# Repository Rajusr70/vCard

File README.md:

# vCard
vCard is an business card with 12 x 8 LED-Matrix (total 96 LEDs) and microcontroller.
The device is pre-programmed with the Arduino Bootloader and powered by a CR2032 button cell.

## Shop
* [vCard](http://www.watterott.com/en/V-Card)

## Hardware
* 
* [Schematics + Layout](https://github.com/watterott/vCard/tree/master/pcb)
* **Note: When using an external power supply (eg via the FTDI port) always remove the battery.**

## Software
* [Arduino Examples](https://github.com/watterott/vCard/tree/master/src)
* [vCard Online Frame Editor](http://vcard.pipefishbook.com/)

## Videos

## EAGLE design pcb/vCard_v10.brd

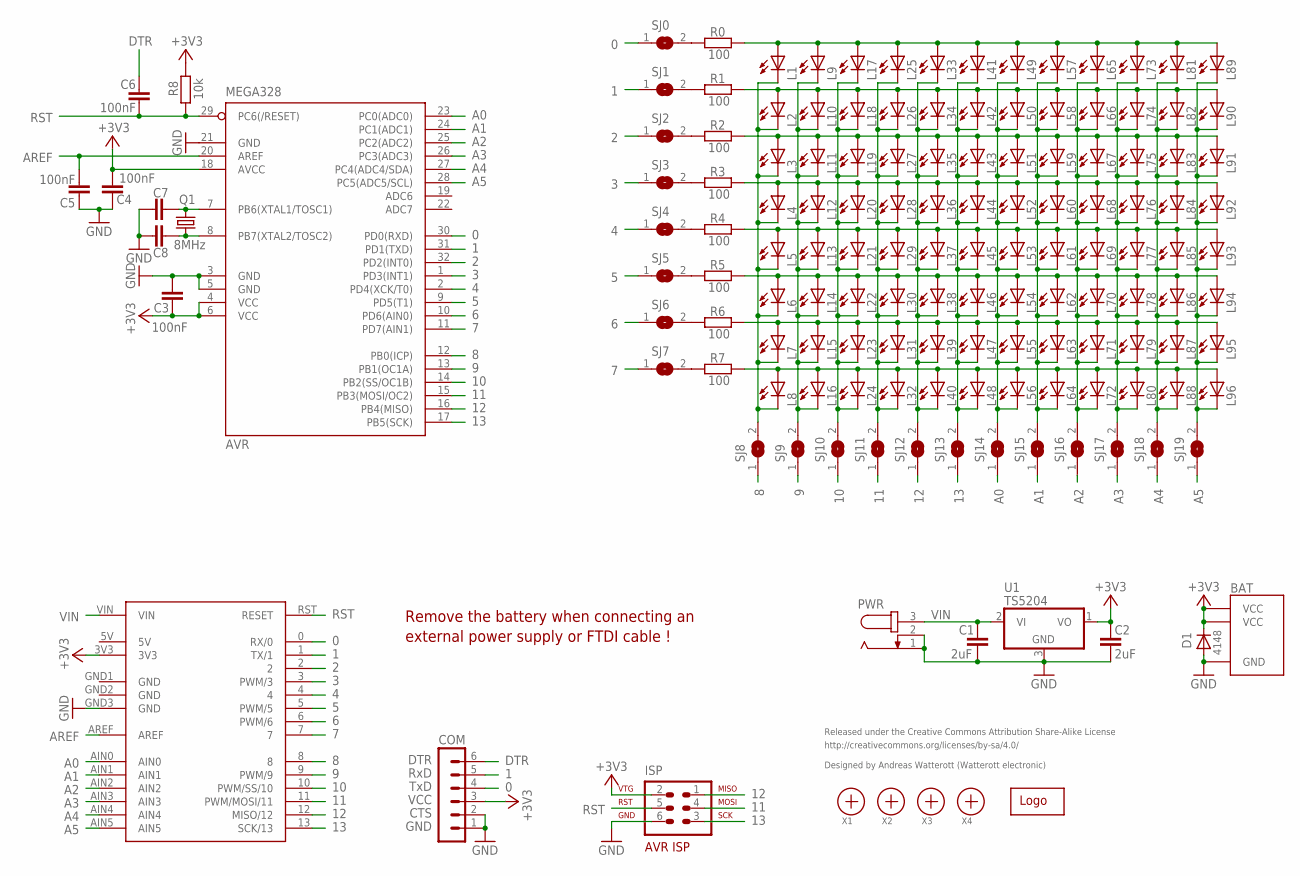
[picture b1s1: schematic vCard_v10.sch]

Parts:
ARDUINO: UNO; DUEMILANOVE2
AVR: MEGA328; TQFP32-08
BAT: KC3002S
C1, C2: 2uF; C0603
C3, C4, C5, C6: 100nF; C0603
C7, C8: C-EUC0603; C0603
COM: MA06-1
D1: 4148; MLL34
ISP: AVR-ISP-6
L1, L2, L3, L4, L5, L6, L7, L8, L9, L10, L11, L12, L13, L14, L15, L16, L17, L18, L19, L20, L21, L22, L23, L24, L25, L26, L27, L28, L29, L30, L31, L32, L33, L34, L35, L36, L37, L38, L39, L40, L41, L42, L43, L44, L45, L46, L47, L48, L49, L50, L51, L52, L53, L54, L55, L56, L57, L58, L59, L60, L61, L62, L63, L64, L65, L66, L67, L68, L69, L70, L71, L72, L73, L74, L75, L76, L77, L78, L79, L80, L81, L82, L83, L84, L85, L86, L87, L88, L89, L90, L91, L92, L93, L94, L95, L96: LEDCHIPLED_0603; CHIPLED_0603
LOGO1: WE-LOGO
PWR: JACK-PLUG0; SPC4077
Q1: 8MHz; HC49/S
R0, R1, R2, R3, R4, R5, R6, R7: 100; R0603
R8: 10k; R0603
SJ0, SJ1, SJ2, SJ3, SJ4, SJ5, SJ6, SJ7, SJ8, SJ9, SJ10, SJ11, SJ12, SJ13, SJ14, SJ15, SJ16, SJ17, SJ18, SJ19: SJ
U1: TS5204; SOT23
X1, X2, X3, X4: PASSER

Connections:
0: ARDUINO.0 (RX/0), AVR.30 (PD0(RXD)), COM.4, SJ0.1
1: ARDUINO.1 (TX/1), AVR.31 (PD1(TXD)), COM.5, SJ1.1
2: ARDUINO.2, AVR.32 (PD2(INT0)), SJ2.1
3: ARDUINO.3 (PWM/3), AVR.1 (PD3(INT1)), SJ3.1
4: ARDUINO.4, AVR.2 (PD4(XCK/T0)), SJ4.1
5: ARDUINO.5 (PWM/5), AVR.9 (PD5(T1)), SJ5.1
5V: ARDUINO.5V
6: ARDUINO.6 (PWM/6), AVR.10 (PD6(AIN0)), SJ6.1
7: ARDUINO.7, AVR.11 (PD7(AIN1)), SJ7.1
8: ARDUINO.8, AVR.12 (PB0(ICP)), SJ8.1
8_: L1.C, L2.C, L3.C, L4.C, L5.C, L6.C, L7.C, L8.C, SJ8.2
9: ARDUINO.9 (PWM/9), AVR.13 (PB1(OC1A)), SJ9.1
9_: L9.C, L10.C, L11.C, L12.C, L13.C, L14.C, L15.C, L16.C, SJ9.2
10: ARDUINO.10 (PWM/SS/10), AVR.14 (PB2(SS/OC1B)), SJ10.1
10_: L17.C, L18.C, L19.C, L20.C, L21.C, L22.C, L23.C, L24.C, SJ10.2
11: ARDUINO.11 (PWM/MOSI/11), AVR.15 (PB3(MOSI/OC2)), ISP.4, SJ11.1
11_: L25.C, L26.C, L27.C, L28.C, L29.C, L30.C, L31.C, L32.C, SJ11.2
12: ARDUINO.12 (MISO/12), AVR.16 (PB4(MISO)), ISP.1, SJ12.1
12_: L33.C, L34.C, L35.C, L36.C, L37.C, L38.C, L39.C, L40.C, SJ12.2
13: ARDUINO.13 (SCK/13), AVR.17 (PB5(SCK)), ISP.3, SJ13.1
13_: L41.C, L42.C, L43.C, L44.C, L45.C, L46.C, L47.C, L48.C, SJ13.2
+3V3: ARDUINO.3V3, AVR.4 (VCC), AVR.6 (VCC), AVR.18 (AVCC), BAT.VCC1 (VCC), BAT.VCC2 (VCC), C2.1, C3.2, C4.2, COM.3, D1.1 (K), ISP.2, R8.2, U1.1 (VO)
A0: ARDUINO.AIN0, AVR.23 (PC0(ADC0)), SJ14.1
A0_: L49.C, L50.C, L51.C, L52.C, L53.C, L54.C, L55.C, L56.C, SJ14.2
A1: ARDUINO.AIN1, AVR.24 (PC1(ADC1)), SJ15.1
A1_: L57.C, L58.C, L59.C, L60.C, L61.C, L62.C, L63.C, L64.C, SJ15.2
A2: ARDUINO.AIN2, AVR.25 (PC2(ADC2)), SJ16.1
A2_: L65.C, L66.C, L67.C, L68.C, L69.C, L70.C, L71.C, L72.C, SJ16.2
A3: ARDUINO.AIN3, AVR.26 (PC3(ADC3)), SJ17.1
A3_: L73.C, L74.C, L75.C, L76.C, L77.C, L78.C, L79.C, L80.C, SJ17.2
A4: ARDUINO.AIN4, AVR.27 (PC4(ADC4/SDA)), SJ18.1
A4_: L81.C, L82.C, L83.C, L84.C, L85.C, L86.C, L87.C, L88.C, SJ18.2
A5: ARDUINO.AIN5, AVR.28 (PC5(ADC5/SCL)), SJ19.1
A5_: L89.C, L90.C, L91.C, L92.C, L93.C, L94.C, L95.C, L96.C, SJ19.2
AREF: ARDUINO.AREF, AVR.20 (AREF), C5.2
DTR: C6.1, COM.6
GND: ARDUINO.GND1 (GND), ARDUINO.GND2 (GND), ARDUINO.GND3 (GND), AVR.3 (GND), AVR.5 (GND), AVR.21 (GND), BAT.GND, C1.2, C2.2, C3.1, C4.1, C5.1, C7.2, C8.2, COM.1, COM.2, D1.2 (A), ISP.6, PWR.1, PWR.2, U1.3 (GND)
unnamed: L1.A, L9.A, L17.A, L25.A, L33.A, L41.A, L49.A, L57.A, L65.A, L73.A, L81.A, L89.A, R0.2
unnamed: AVR.8 (PB7(XTAL2/TOSC2)), C8.1, Q1.1
unnamed: AVR.7 (PB6(XTAL1/TOSC1)), C7.1, Q1.2
unnamed: R0.1, SJ0.2
unnamed: R1.1, SJ1.2
unnamed: R2.1, SJ2.2
unnamed: R3.1, SJ3.2
unnamed: R4.1, SJ4.2
unnamed: R5.1, SJ5.2
unnamed: R6.1, SJ6.2
unnamed: R7.1, SJ7.2
unnamed: L2.A, L10.A, L18.A, L26.A, L34.A, L42.A, L50.A, L58.A, L66.A, L74.A, L82.A, L90.A, R1.2
unnamed: L3.A, L11.A, L19.A, L27.A, L35.A, L43.A, L51.A, L59.A, L67.A, L75.A, L83.A, L91.A, R2.2
unnamed: L4.A, L12.A, L20.A, L28.A, L36.A, L44.A, L52.A, L60.A, L68.A, L76.A, L84.A, L92.A, R3.2
unnamed: L5.A, L13.A, L21.A, L29.A, L37.A, L45.A, L53.A, L61.A, L69.A, L77.A, L85.A, L93.A, R4.2
unnamed: L6.A, L14.A, L22.A, L30.A, L38.A, L46.A, L54.A, L62.A, L70.A, L78.A, L86.A, L94.A, R5.2
unnamed: L7.A, L15.A, L23.A, L31.A, L39.A, L47.A, L55.A, L63.A, L71.A, L79.A, L87.A, L95.A, R6.2
unnamed: L8.A, L16.A, L24.A, L32.A, L40.A, L48.A, L56.A, L64.A, L72.A, L80.A, L88.A, L96.A, R7.2
RST: ARDUINO.RST (RESET), AVR.29 (PC6(/RESET)), C6.2, ISP.5, R8.1
VIN: ARDUINO.VIN, C1.1, PWR.3, U1.2 (VI)

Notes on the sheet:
Released under the Creative Commons Attribution Share-Alike License
http://creativecommons.org/licenses/by-sa/4.0/
Designed by Andreas Watterott (Watterott electronic)
GND
CTS
VCC
TxD
RxD
DTR
Remove the battery when connecting an
external power supply or FTDI cable !

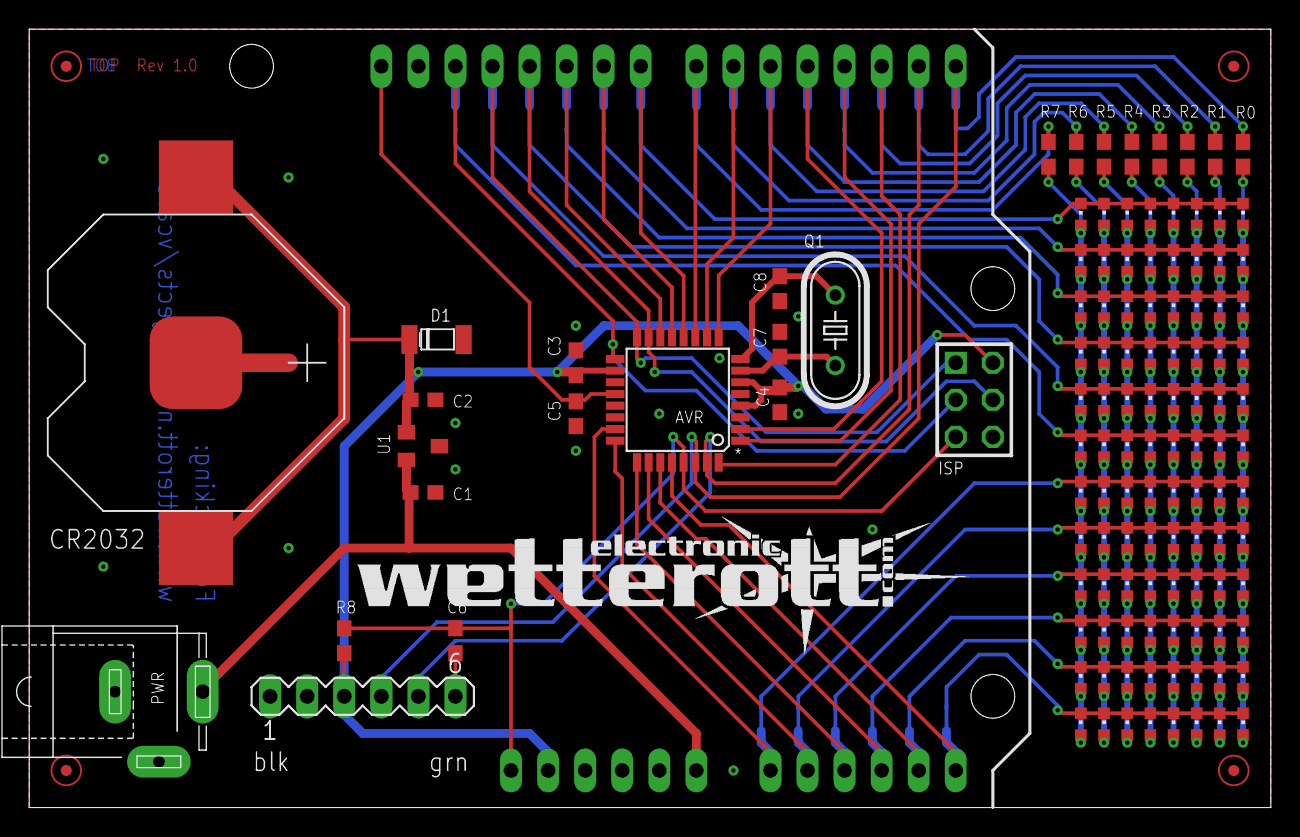
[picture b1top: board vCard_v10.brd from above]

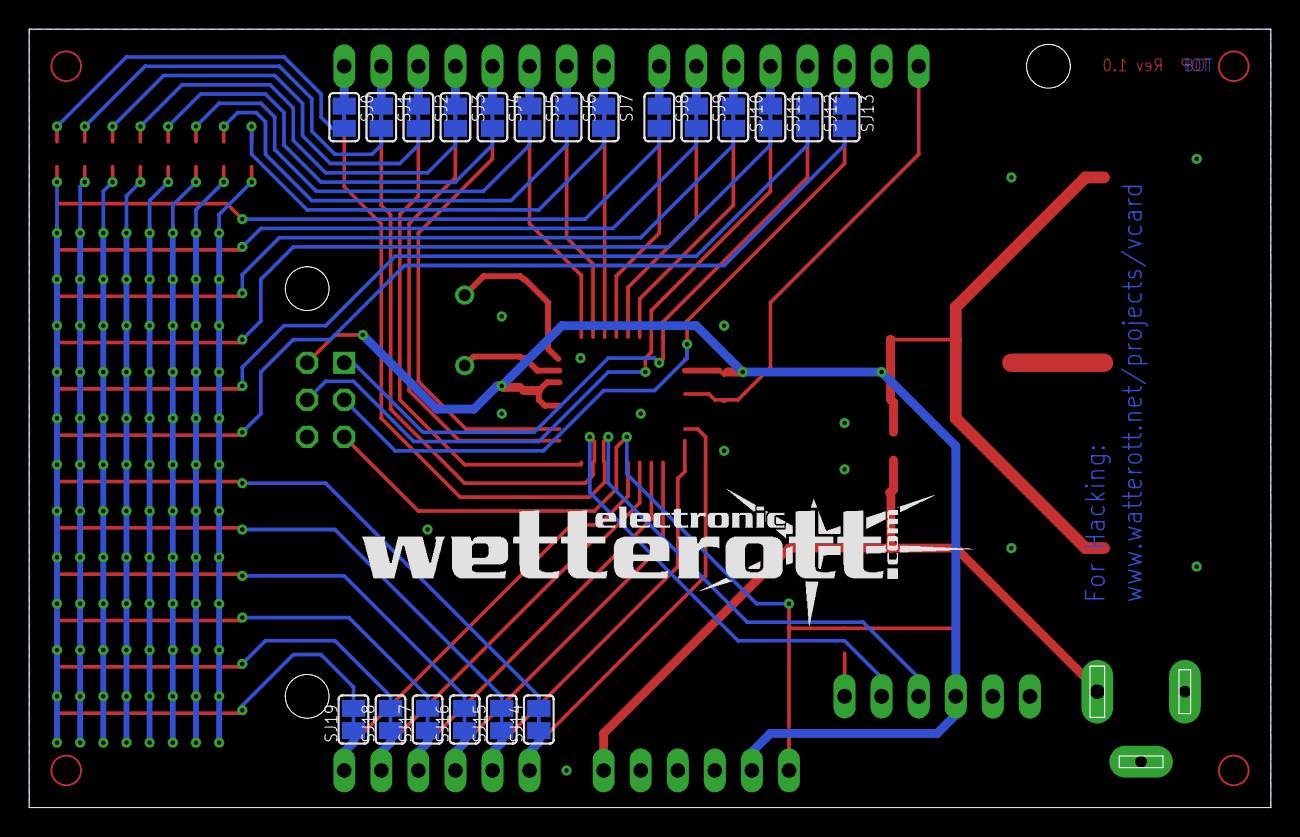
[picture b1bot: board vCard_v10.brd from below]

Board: 2 copper layers, 85.1 x 53.3 mm, 148 parts (21 on the bottom side), 56 nets.

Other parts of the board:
LOGO: WE-LOGO

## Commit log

2012-03-10 source and layout files
2012-07-13 added PDF schematic
2012-11-26 updated schematics
2013-09-21 updated hardware diagram
2014-03-10 updated license infos
2014-11-06 cleaned up schematics and layout
2015-01-11 moved image
2015-01-11 renamed image
